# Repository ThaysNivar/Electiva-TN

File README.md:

Repositorio Diseño Mecatronico
Thays Nivar 2022-0459

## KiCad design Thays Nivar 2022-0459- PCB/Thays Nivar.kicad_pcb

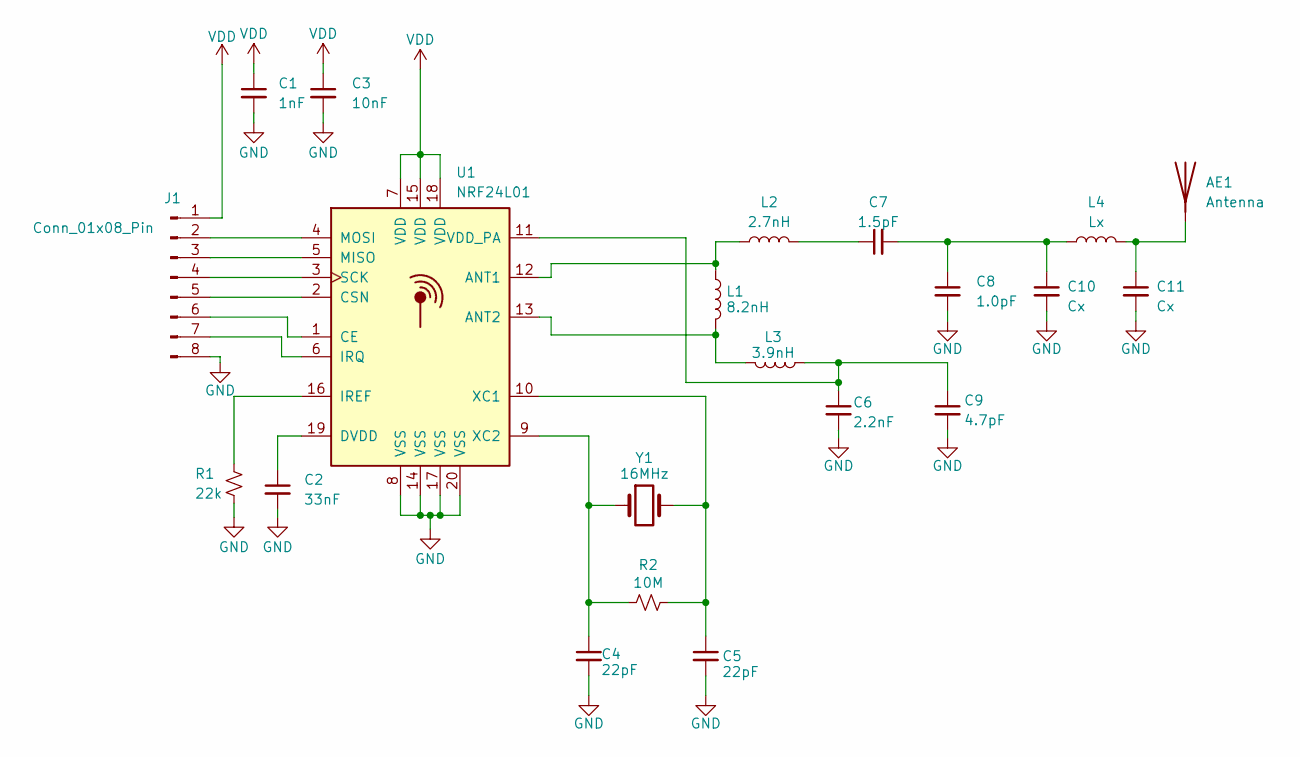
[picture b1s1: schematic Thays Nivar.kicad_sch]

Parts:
AE1: Antenna; Texas_SWRA117D_2.4GHz_Right
C1: 1nF; C_0402_1005Metric
C2: 33nF; C_0402_1005Metric
C3: 10nF; C_0402_1005Metric
C4, C5: 22pF; C_0402_1005Metric
C6: 2.2nF; C_0402_1005Metric
C7: 1.5pF; C_0402_1005Metric
C8: 1.0pF; C_0402_1005Metric
C9: 4.7pF; C_0402_1005Metric
C10, C11: Cx; C_0402_1005Metric
J1: Conn_01x08_Pin; Hirose_DF13-08P-1.25DSA_1x08_P1.25mm_Vertical
L1: 8.2nH; L_0402_1005Metric
L2: 2.7nH; L_0402_1005Metric
L3: 3.9nH; L_0402_1005Metric
L4: Lx; L_0402_1005Metric
R1: 22k; R_0402_1005Metric
R2: 10M; R_0402_1005Metric
U1: NRF24L01; QFN-20-1EP_4x4mm_P0.5mm_EP2.5x2.5mm
Y1: 16MHz; Crystal_SMD_3215-2Pin_3.2x1.5mm

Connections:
GND: C1.2, C2.2, C3.2, C4.2, C5.2, C6.2, C8.2, C9.2, C10.2, C11.2, J1.8, R1.2, U1.8 (VSS), U1.14 (VSS), U1.17 (VSS), U1.20 (VSS)
unnamed: AE1.1 (A), C11.1, L4.2
unnamed: C7.1, L2.2
unnamed: C7.2, C8.1, C10.1, L4.1
unnamed: J1.2, U1.4 (MOSI)
unnamed: J1.3, U1.5 (MISO)
unnamed: J1.4, U1.3 (SCK)
unnamed: J1.5, U1.2 (CSN)
unnamed: J1.6, U1.1 (CE)
unnamed: J1.7, U1.6 (IRQ)
unnamed: L1.1, L2.1, U1.12 (ANT1)
unnamed: L1.2, L3.2, U1.13 (ANT2)
unnamed: C2.1, U1.19 (DVDD)
unnamed: R1.1, U1.16 (IREF)
unnamed: C6.1, C9.1, L3.1, U1.11 (VDD_PA)
unnamed: C5.1, R2.2, U1.10 (XC1), Y1.2
unnamed: C4.1, R2.1, U1.9 (XC2), Y1.1
VDD: C1.1, C3.1, J1.1, U1.7 (VDD), U1.15 (VDD), U1.18 (VDD)

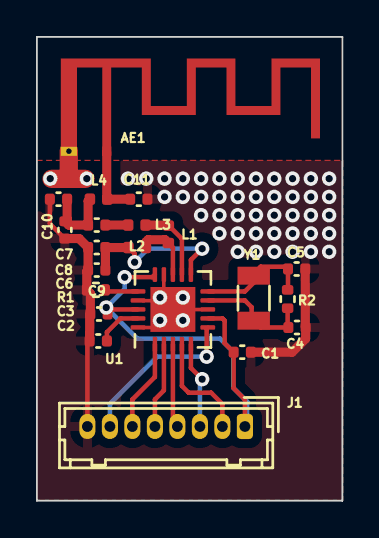
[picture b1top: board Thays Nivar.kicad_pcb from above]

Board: 2 copper layers, 17.0 x 25.8 mm, 21 parts (0 on the bottom side), 18 nets.

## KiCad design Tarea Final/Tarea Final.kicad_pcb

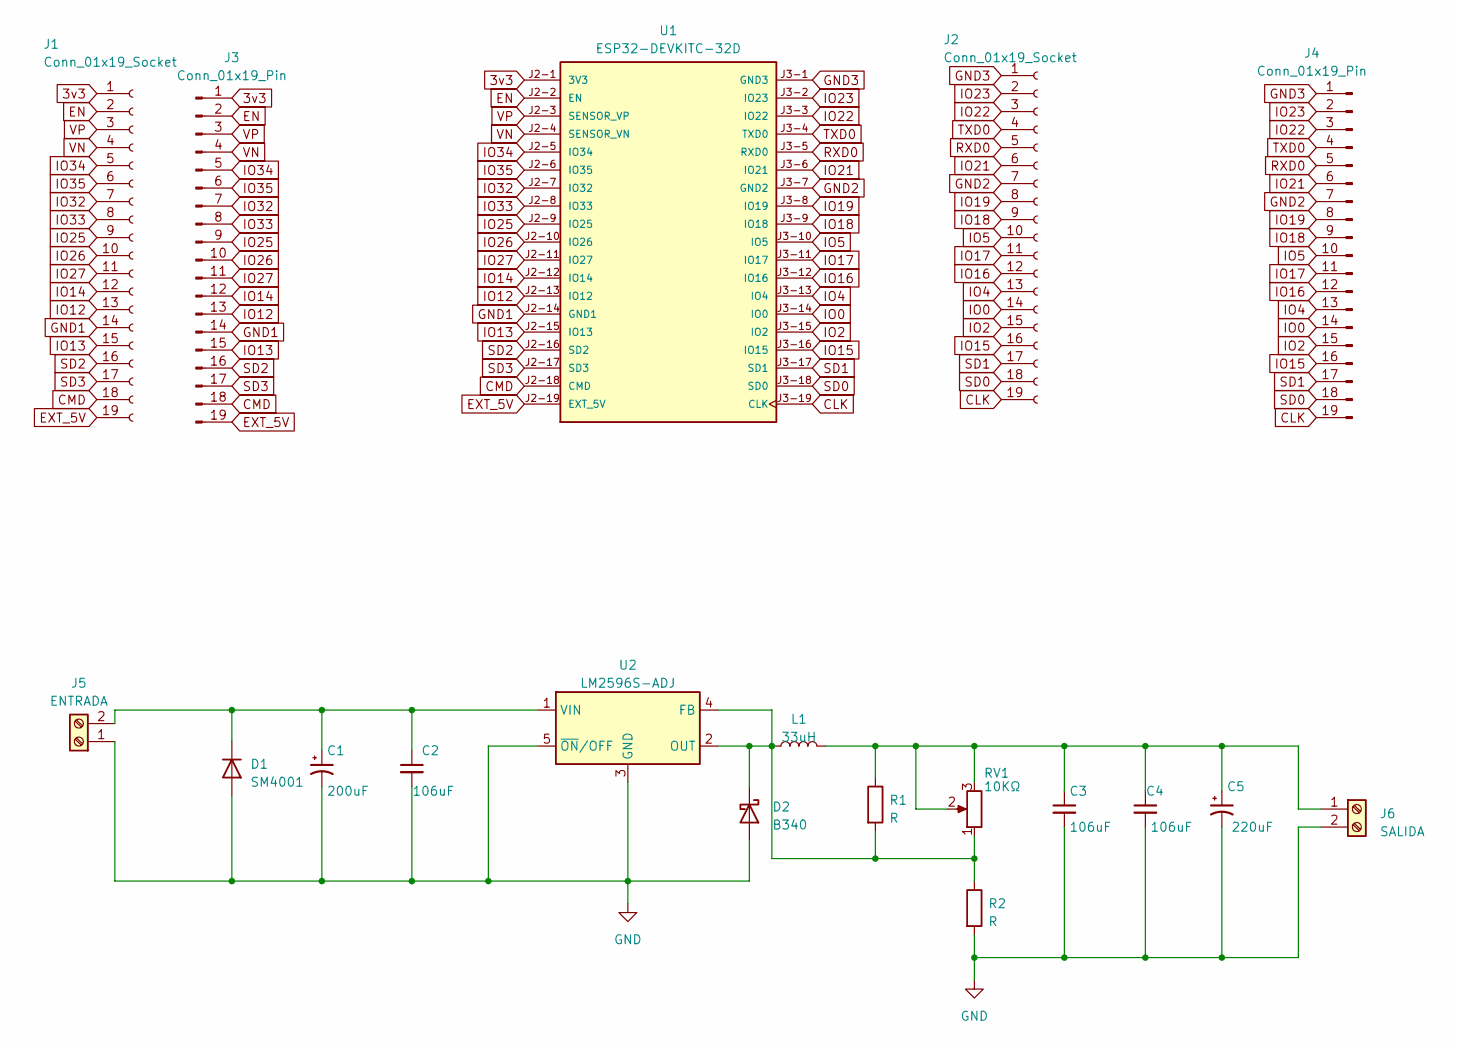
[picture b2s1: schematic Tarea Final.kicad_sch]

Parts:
C1: 200uF; CP_Elec_6.3x5.2
C2, C3, C4: 106uF; C_Disc_D8.0mm_W2.5mm_P5.00mm
C5: 220uF; CP_Elec_6.3x5.2
D1: SM4001; D_MELF
D2: B340; D_SMC
J1: Conn_01x19_Socket; Altech_AK300_1x19_P5.00mm_45-Degree
J2: Conn_01x19_Socket; PinHeader_1x19_P2.54mm_Vertical
J3: Conn_01x19_Pin; PinHeader_1x19_P2.54mm_Vertical
J4: Conn_01x19_Pin; Altech_AK300_1x19_P5.00mm_45-Degree
J5: ENTRADA; TerminalBlock_bornier-2_P5.08mm
J6: SALIDA; TerminalBlock_bornier-2_P5.08mm
L1: 33uH; L_12x12mm_H6mm
R1, R2: R; R_0603_1608Metric
RV1: 10KΩ; TRIM_COM-09806
U1: ESP32-DEVKITC-32D; MODULE_ESP32-DEVKITC-32D; PARTREV V4
U2: LM2596S-ADJ; TO-263-5_TabPin3

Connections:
3v3: J1.1, J3.1, U1.J2-1 (3V3)
CLK: J2.19, J4.19, U1.J3-19 (CLK)
CMD: J1.18, J3.18, U1.J2-18 (CMD)
EN: J1.2, J3.2, U1.J2-2 (EN)
EXT_5V: J1.19, J3.19, U1.J2-19 (EXT_5V)
GND: C1.2, C2.2, C3.2, C4.2, C5.2, D1.2 (A), D2.2 (A), J5.1, J6.2, R2.2, U2.3 (GND), U2.5 (~ON/OFF)
GND1: J1.14, J3.14, U1.J2-14 (GND1)
GND2: J2.7, J4.7, U1.J3-7 (GND2)
GND3: J2.1, J4.1, U1.J3-1 (GND3)
IO0: J2.14, J4.14, U1.J3-14 (IO0)
IO2: J2.15, J4.15, U1.J3-15 (IO2)
IO4: J2.13, J4.13, U1.J3-13 (IO4)
IO5: J2.10, J4.10, U1.J3-10 (IO5)
IO12: J1.13, J3.13, U1.J2-13 (IO12)
IO13: J1.15, J3.15, U1.J2-15 (IO13)
IO14: J1.12, J3.12, U1.J2-12 (IO14)
IO15: J2.16, J4.16, U1.J3-16 (IO15)
IO16: J2.12, J4.12, U1.J3-12 (IO16)
IO17: J2.11, J4.11, U1.J3-11 (IO17)
IO18: J2.9, J4.9, U1.J3-9 (IO18)
IO19: J2.8, J4.8, U1.J3-8 (IO19)
IO21: J2.6, J4.6, U1.J3-6 (IO21)
IO22: J2.3, J4.3, U1.J3-3 (IO22)
IO23: J2.2, J4.2, U1.J3-2 (IO23)
IO25: J1.9, J3.9, U1.J2-9 (IO25)
IO26: J1.10, J3.10, U1.J2-10 (IO26)
IO27: J1.11, J3.11, U1.J2-11 (IO27)
IO32: J1.7, J3.7, U1.J2-7 (IO32)
IO33: J1.8, J3.8, U1.J2-8 (IO33)
IO34: J1.5, J3.5, U1.J2-5 (IO34)
IO35: J1.6, J3.6, U1.J2-6 (IO35)
unnamed: C1.1, C2.1, D1.1 (K), J5.2, U2.1 (VIN)
unnamed: D2.1 (K), L1.1, R1.2, R2.1, RV1.1, U2.2 (OUT), U2.4 (FB)
unnamed: C3.1, C4.1, C5.1, J6.1, L1.2, R1.1, RV1.2, RV1.3
RXD0: J2.5, J4.5, U1.J3-5 (RXD0)
SD0: J2.18, J4.18, U1.J3-18 (SD0)
SD1: J2.17, J4.17, U1.J3-17 (SD1)
SD2: J1.16, J3.16, U1.J2-16 (SD2)
SD3: J1.17, J3.17, U1.J2-17 (SD3)
TXD0: J2.4, J4.4, U1.J3-4 (TXD0)
VN: J1.4, J3.4, U1.J2-4 (SENSOR_VN)
VP: J1.3, J3.3, U1.J2-3 (SENSOR_VP)

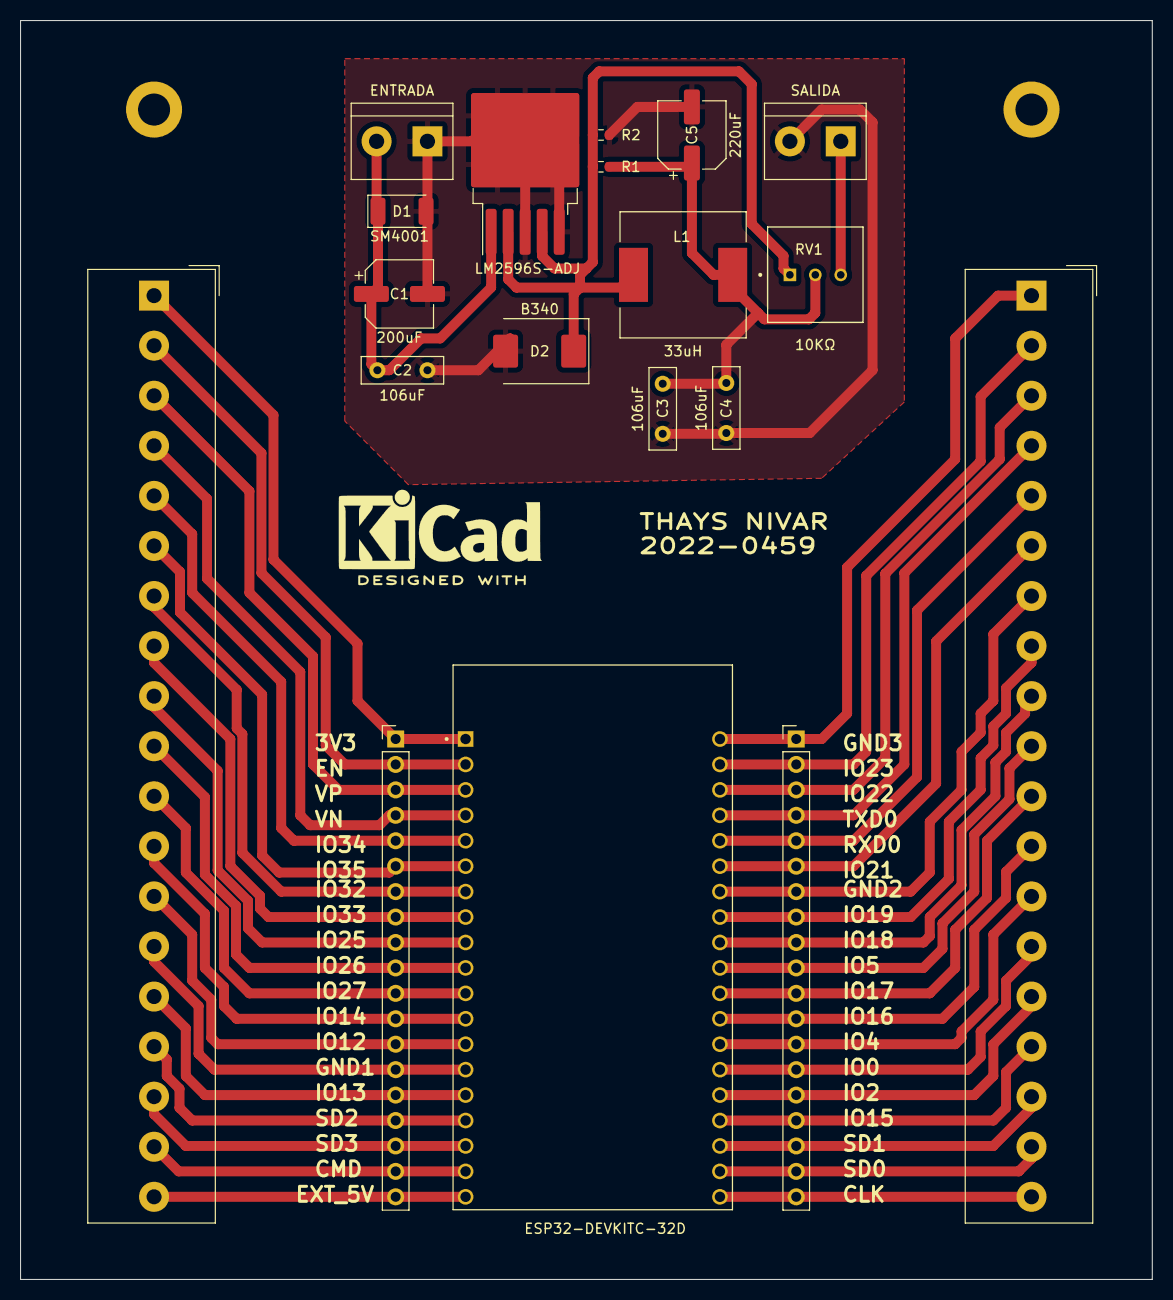
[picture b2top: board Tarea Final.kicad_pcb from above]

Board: 2 copper layers, 113.0 x 125.7 mm, 19 parts (0 on the bottom side), 42 nets.

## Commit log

2024-12-10 Create Link del Video
